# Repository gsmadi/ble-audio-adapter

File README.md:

# ble-audio-adapter

The three deliverable files are the following:

- Schematic: ble-audio-adapter.sch
- PCB: ble-audio-adapter.kicad_pcb
- CAD: ble-audio.stl

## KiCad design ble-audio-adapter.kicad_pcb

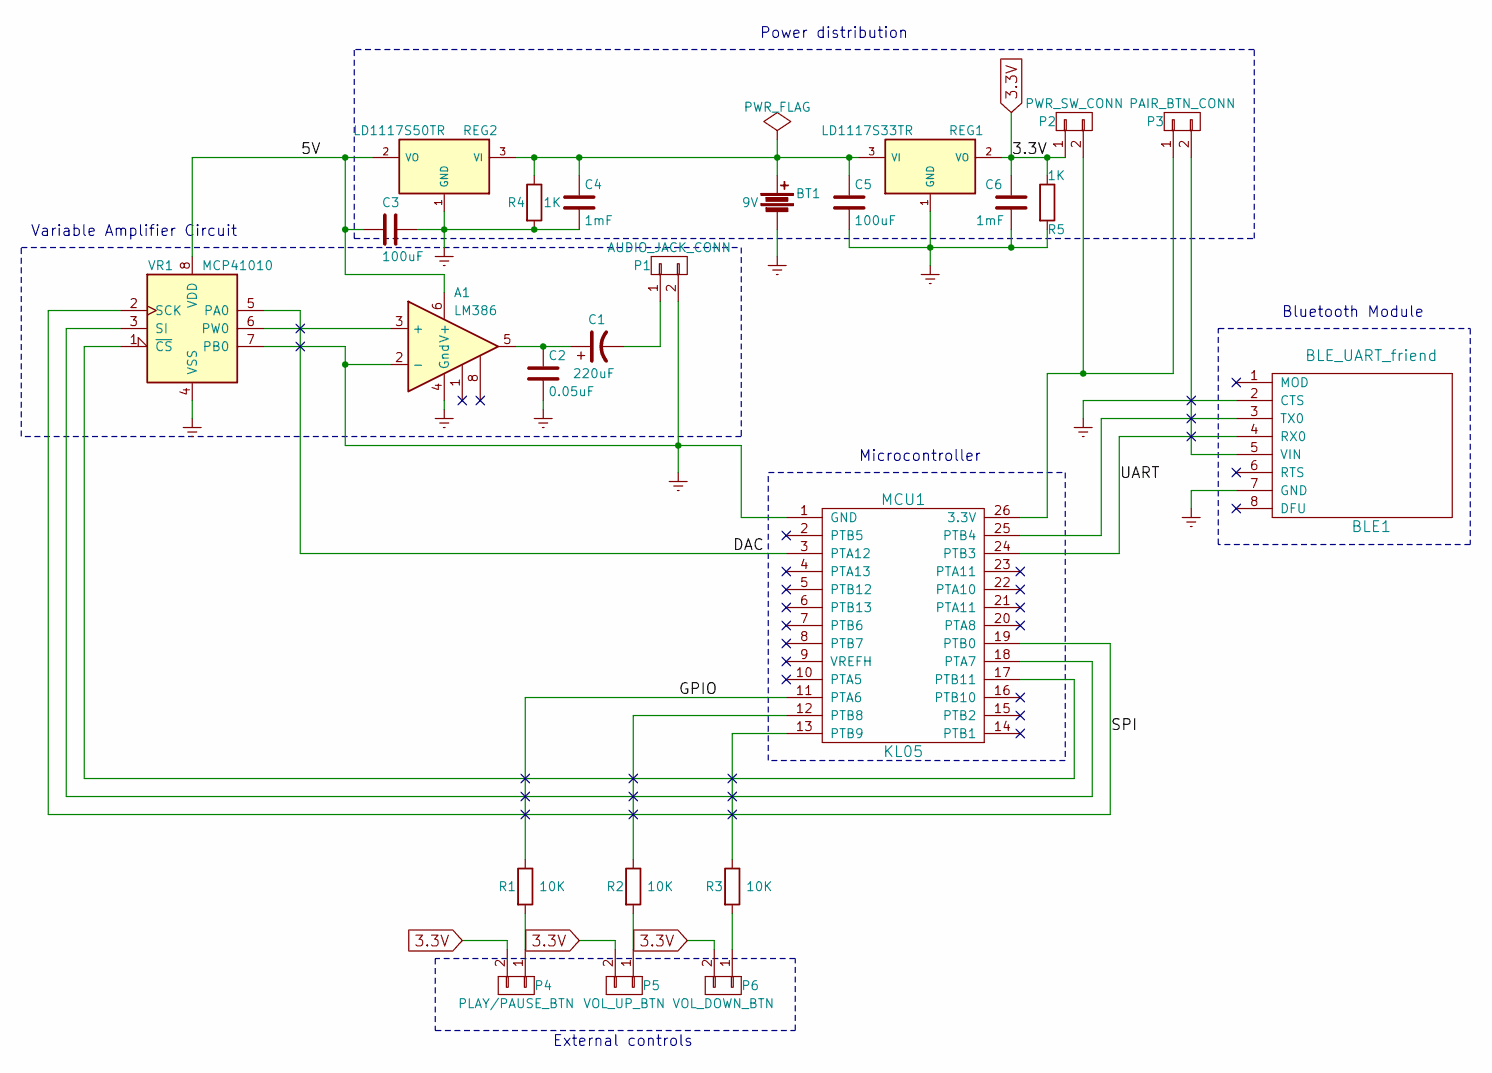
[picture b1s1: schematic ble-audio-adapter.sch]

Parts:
A1: LM386; SOIC-8-N
BLE1: BLE_UART_friend; Socket_Strip_Straight_1x08
BT1: 9V; Battery_Connector
C1: 220uF; TantalC_SizeB_EIA-3528_HandSoldering
C2: 0.05uF; C_1206
C3, C5: 100uF; C_1206
C4, C6: 1mF; C_1206
MCU1: KL05; DIP-26_W15.24mm
P1: AUDIO_JACK_CONN; Pin_Header_Straight_1x02
P2: PWR_SW_CONN; Pin_Header_Straight_1x02
P3: PAIR_BTN_CONN; Pin_Header_Straight_1x02
P4: PLAY/PAUSE_BTN; Pin_Header_Straight_1x02
P5: VOL_UP_BTN; Pin_Header_Straight_1x02
P6: VOL_DOWN_BTN; Pin_Header_Straight_1x02
R1, R2, R3: 10K; R_0603_HandSoldering
R4, R5: 1K; R_0603_HandSoldering
REG1: LD1117S33TR; SOT-223
REG2: LD1117S50TR; SOT-223
VR1: MCP41010; SOIC-8-N

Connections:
3.3V: C6.1, P2.1, P4.2, P5.2, P6.2, R5.1, REG1.2 (VO)
/5V: A1.6 (V+), C3.2, REG2.2 (VO), VR1.8 (VDD)
/DAC: MCU1.3 (PTA12), VR1.5 (PA0)
/GPIO: MCU1.11 (PTA6), R1.1
/SPI: MCU1.19 (PTB0), VR1.2 (SCK)
/UART: BLE1.4 (RX0), MCU1.24 (PTB3)
GNDREF: A1.2 (-), A1.4 (Gnd), BLE1.2 (CTS), BLE1.7 (GND), BT1.2, C2.2, C3.1, C4.2, C5.2, C6.2, MCU1.1 (GND), P1.2, R4.2, R5.2, REG1.1 (GND), REG2.1 (GND), VR1.4 (VSS), VR1.7 (PB0)
unnamed: A1.3 (+), VR1.6 (PW0)
unnamed: A1.5, C1.1, C2.1
unnamed: BLE1.3 (TX0), MCU1.25 (PTB4)
unnamed: BLE1.5 (VIN), P3.2
unnamed: BT1.1, C4.1, C5.1, R4.1, REG1.3 (VI), REG2.3 (VI)
unnamed: C1.2, P1.1
unnamed: MCU1.12 (PTB8), R2.1
unnamed: MCU1.13 (PTB9), R3.1
unnamed: MCU1.17 (PTB11), VR1.1 (~CS)
unnamed: MCU1.18 (PTA7), VR1.3 (SI)
unnamed: MCU1.26 (3.3V), P2.2, P3.1
unnamed: P4.1, R1.2
unnamed: P5.1, R2.2
unnamed: P6.1, R3.2

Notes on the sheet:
Bluetooth Module
Microcontroller
Variable Amplifier Circuit
Power distribution
External controls

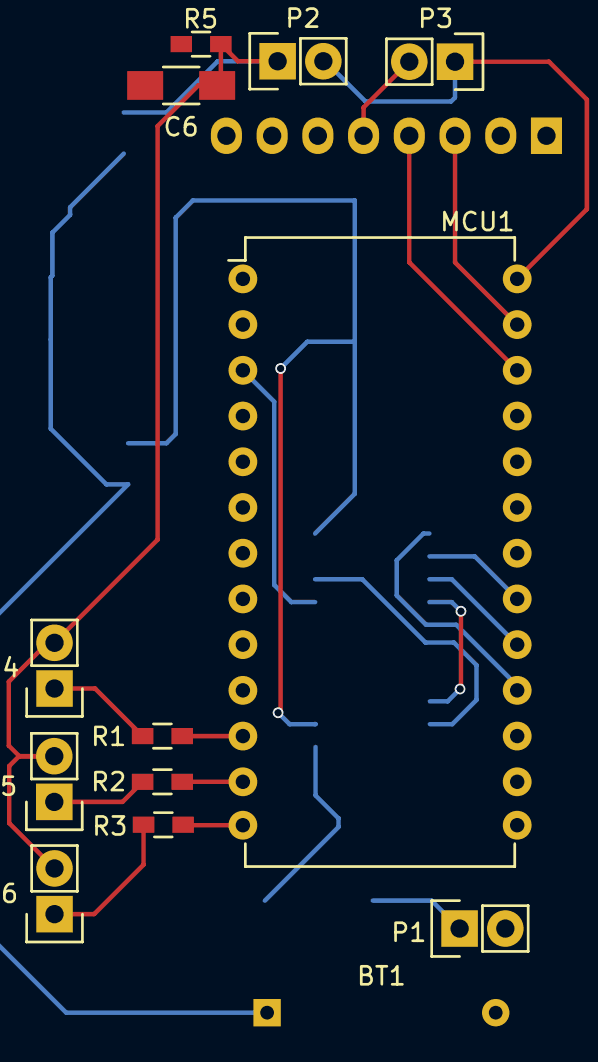
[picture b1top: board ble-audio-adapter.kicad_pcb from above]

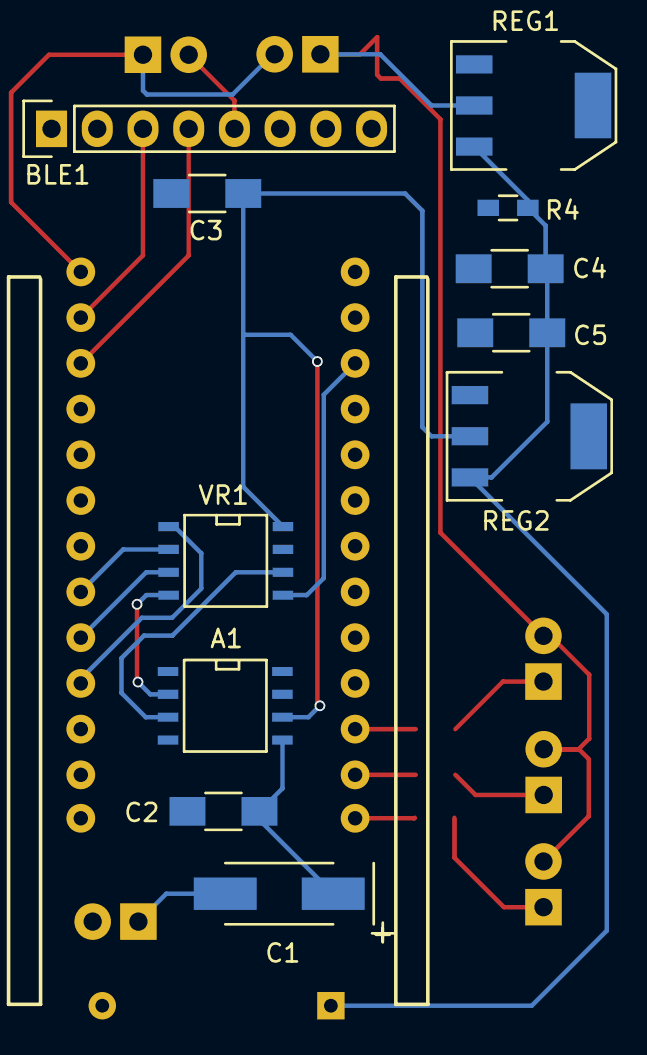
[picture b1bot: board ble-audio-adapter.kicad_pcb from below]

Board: 2 copper layers, 24 parts (11 on the bottom side), 21 nets.

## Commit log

2016-10-29 Finished schematic
2016-10-30 Add rescue component lib
2016-10-30 Updated reference positioning
2016-10-30 Completed Revision-1
2016-11-21 Final CAD packages
